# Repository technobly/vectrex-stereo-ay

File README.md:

Vectrex Stereo AY
===

A simple PCB to turn your Vectrex AY-3-8912 3-channel mono sound into stereo line out!

How does it sound?
===

[Check out my Youtube demo](https://www.youtube.com/watch?v=SDDFqmjVvJo&ab_channel=BDub)

How to Use
===

- Refer to Installation Pics below
- Remove your AY-3-8912 from its socket
- Plug the AY-3-8912 into this adapter
- Plug this adapter into the AY's socket
- Clip the micro grabber on 
    - 2GE: Clip onto the bottom of R329 as pictured below.
    - 3GE: Clip on the same place or R329, which is just a jumper wire.
- Plug into your favorite amplifier and enjoy!

BOM and Parts ordering
===

- 1x - 1 x 14 male machine pin header [10PCS 40 Pin 2.54mm Single Row Round Male Pin Header machined J8](https://www.ebay.com/itm/373634328180)
- 1x - 28-pin DIP wide machined pin socket [10Pcs 2.54mm Pitch 28 Pin DIP Round Pin Solder IC Socket Adaptor Wide](https://www.ebay.com/itm/182182186937)
- 2x - 15k 1% 0805
- 2x - 10k 1% 0805
- 2x - 0.22uF 0805
- 2x - 2.2nF 0805
- 1x - Micro grabber [-> get something like this one <-](https://www.amazon.com/Minigrabber-Clip-Test-Wires-colors/dp/B01H5UMZXM) ... [X avoid this style X](https://www.amazon.com/DIYhz-Colors-Grabbers-Electronic-Experiment/dp/B07BCZSNGS)
- 1x - [3.5mm Female Stereo audio pigtail](https://www.amazon.com/gp/product/B082VVWND3)

Installation Pics
===

Ordering PCB's
===

OSHPark is a good place to order with purple or the new "after dark" theme color scheme.  You can upload the KiCad `vectrex-stereo-ay.kicad_pcb` there directly.  I would download this entire Github repo ZIP file first though instead of just trying to save the PCB file from your browser.

Another way to order PCB's is by using the included [gerbers-tall-design](gerbers/vectrex-stereo-ay-v1.0.zip) and uploading those with all of the necessary specs to companies like [PCBWay](https://www.pcbway.com) or [JLCPCB](https://jlcpcb.com)

LICENSE
===

Attribution-NonCommercial-ShareAlike 4.0 International (CC BY-NC-SA 4.0)

Basically, you can make, use, remix as long as you give credit... but you are not allowed to sell them for profit.
[If you like this project, buy me a coffee please!](https://buymeacoffee.com/walach)  Full [LICENSE here](LICENSE)

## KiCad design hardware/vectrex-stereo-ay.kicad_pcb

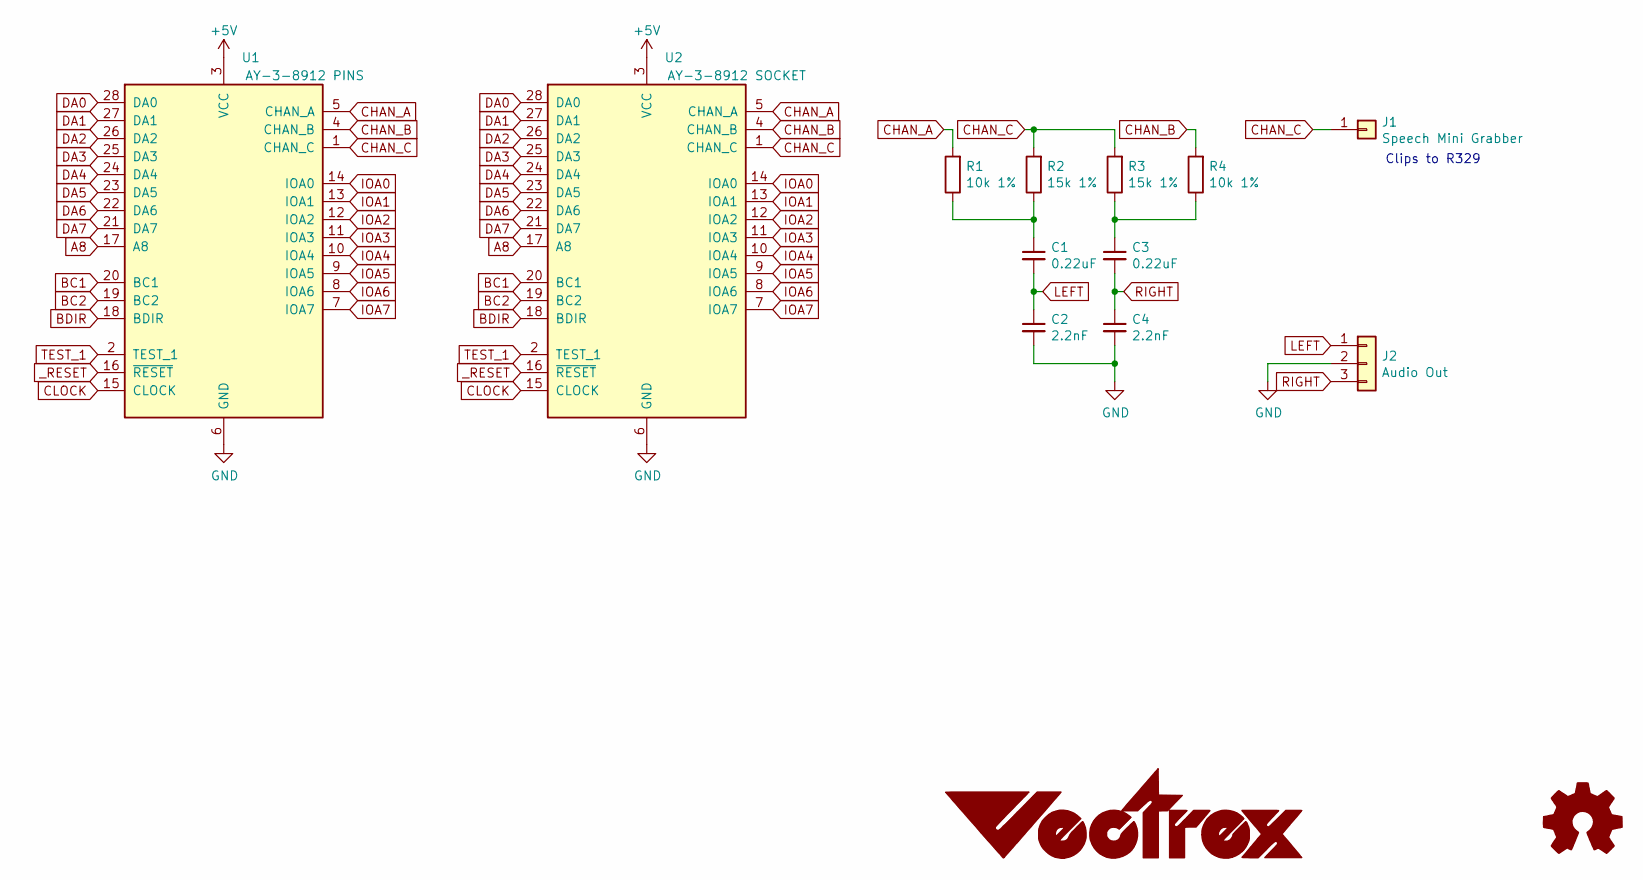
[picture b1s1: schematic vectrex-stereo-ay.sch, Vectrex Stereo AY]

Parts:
C1, C3: 0.22uF; R_0805_2012Metric_Pad1.15x1.40mm_HandSolder
C2, C4: 2.2nF; R_0805_2012Metric_Pad1.15x1.40mm_HandSolder
J1: Speech Mini Grabber; PinHeader_1x01_P2.54mm_Vertical
J2: Audio Out; PinHeader_1x03_P2.54mm_Vertical
R1, R4: 10k 1%; R_0805_2012Metric_Pad1.15x1.40mm_HandSolder
R2, R3: 15k 1%; R_0805_2012Metric_Pad1.15x1.40mm_HandSolder
U1: AY-3-8912 PINS; DIP-28_W15.24mm-pins
U2: AY-3-8912 SOCKET; DIP-28_W15.24mm-socket

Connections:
+5V: U1.3 (VCC), U2.3 (VCC)
A8: U1.17 (A8), U2.17 (A8)
BC1: U1.20 (BC1), U2.20 (BC1)
BC2: U1.19 (BC2), U2.19 (BC2)
BDIR: U1.18 (BDIR), U2.18 (BDIR)
CHAN_A: R1.2, U1.5 (CHAN_A), U2.5 (CHAN_A)
CHAN_B: R4.2, U1.4 (CHAN_B), U2.4 (CHAN_B)
CHAN_C: J1.1, R2.2, R3.2, U1.1 (CHAN_C), U2.1 (CHAN_C)
CLOCK: U1.15 (CLOCK), U2.15 (CLOCK)
DA0: U1.28 (DA0), U2.28 (DA0)
DA1: U1.27 (DA1), U2.27 (DA1)
DA2: U1.26 (DA2), U2.26 (DA2)
DA3: U1.25 (DA3), U2.25 (DA3)
DA4: U1.24 (DA4), U2.24 (DA4)
DA5: U1.23 (DA5), U2.23 (DA5)
DA6: U1.22 (DA6), U2.22 (DA6)
DA7: U1.21 (DA7), U2.21 (DA7)
GND: C2.2, C4.2, J2.2, U1.6 (GND), U2.6 (GND)
IOA0: U1.14 (IOA0), U2.14 (IOA0)
IOA1: U1.13 (IOA1), U2.13 (IOA1)
IOA2: U1.12 (IOA2), U2.12 (IOA2)
IOA3: U1.11 (IOA3), U2.11 (IOA3)
IOA4: U1.10 (IOA4), U2.10 (IOA4)
IOA5: U1.9 (IOA5), U2.9 (IOA5)
IOA6: U1.8 (IOA6), U2.8 (IOA6)
IOA7: U1.7 (IOA7), U2.7 (IOA7)
LEFT: C1.2, C2.1, J2.1
unnamed: C1.1, R1.1, R2.1
unnamed: C3.1, R3.1, R4.1
RIGHT: C3.2, C4.1, J2.3
TEST_1: U1.2 (TEST_1), U2.2 (TEST_1)
_RESET: U1.16 (~RESET~), U2.16 (~RESET~)

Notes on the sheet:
Clips to R329

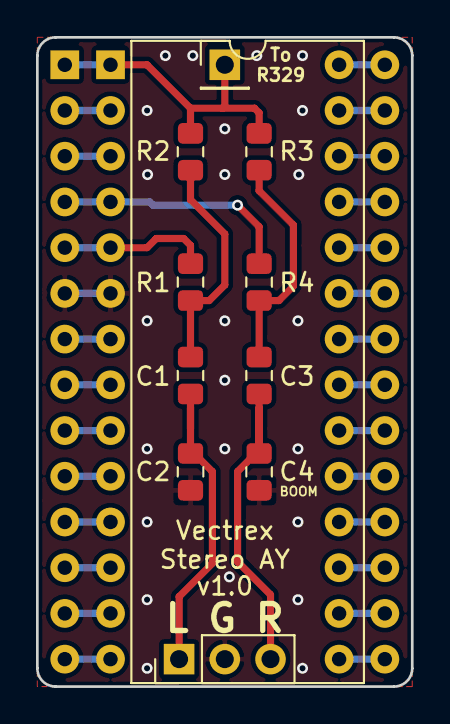
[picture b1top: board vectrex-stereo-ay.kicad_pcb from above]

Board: 2 copper layers, 20.8 x 36.1 mm, 12 parts (0 on the bottom side), 32 nets.

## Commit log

2021-07-21 initial revision v1.0
